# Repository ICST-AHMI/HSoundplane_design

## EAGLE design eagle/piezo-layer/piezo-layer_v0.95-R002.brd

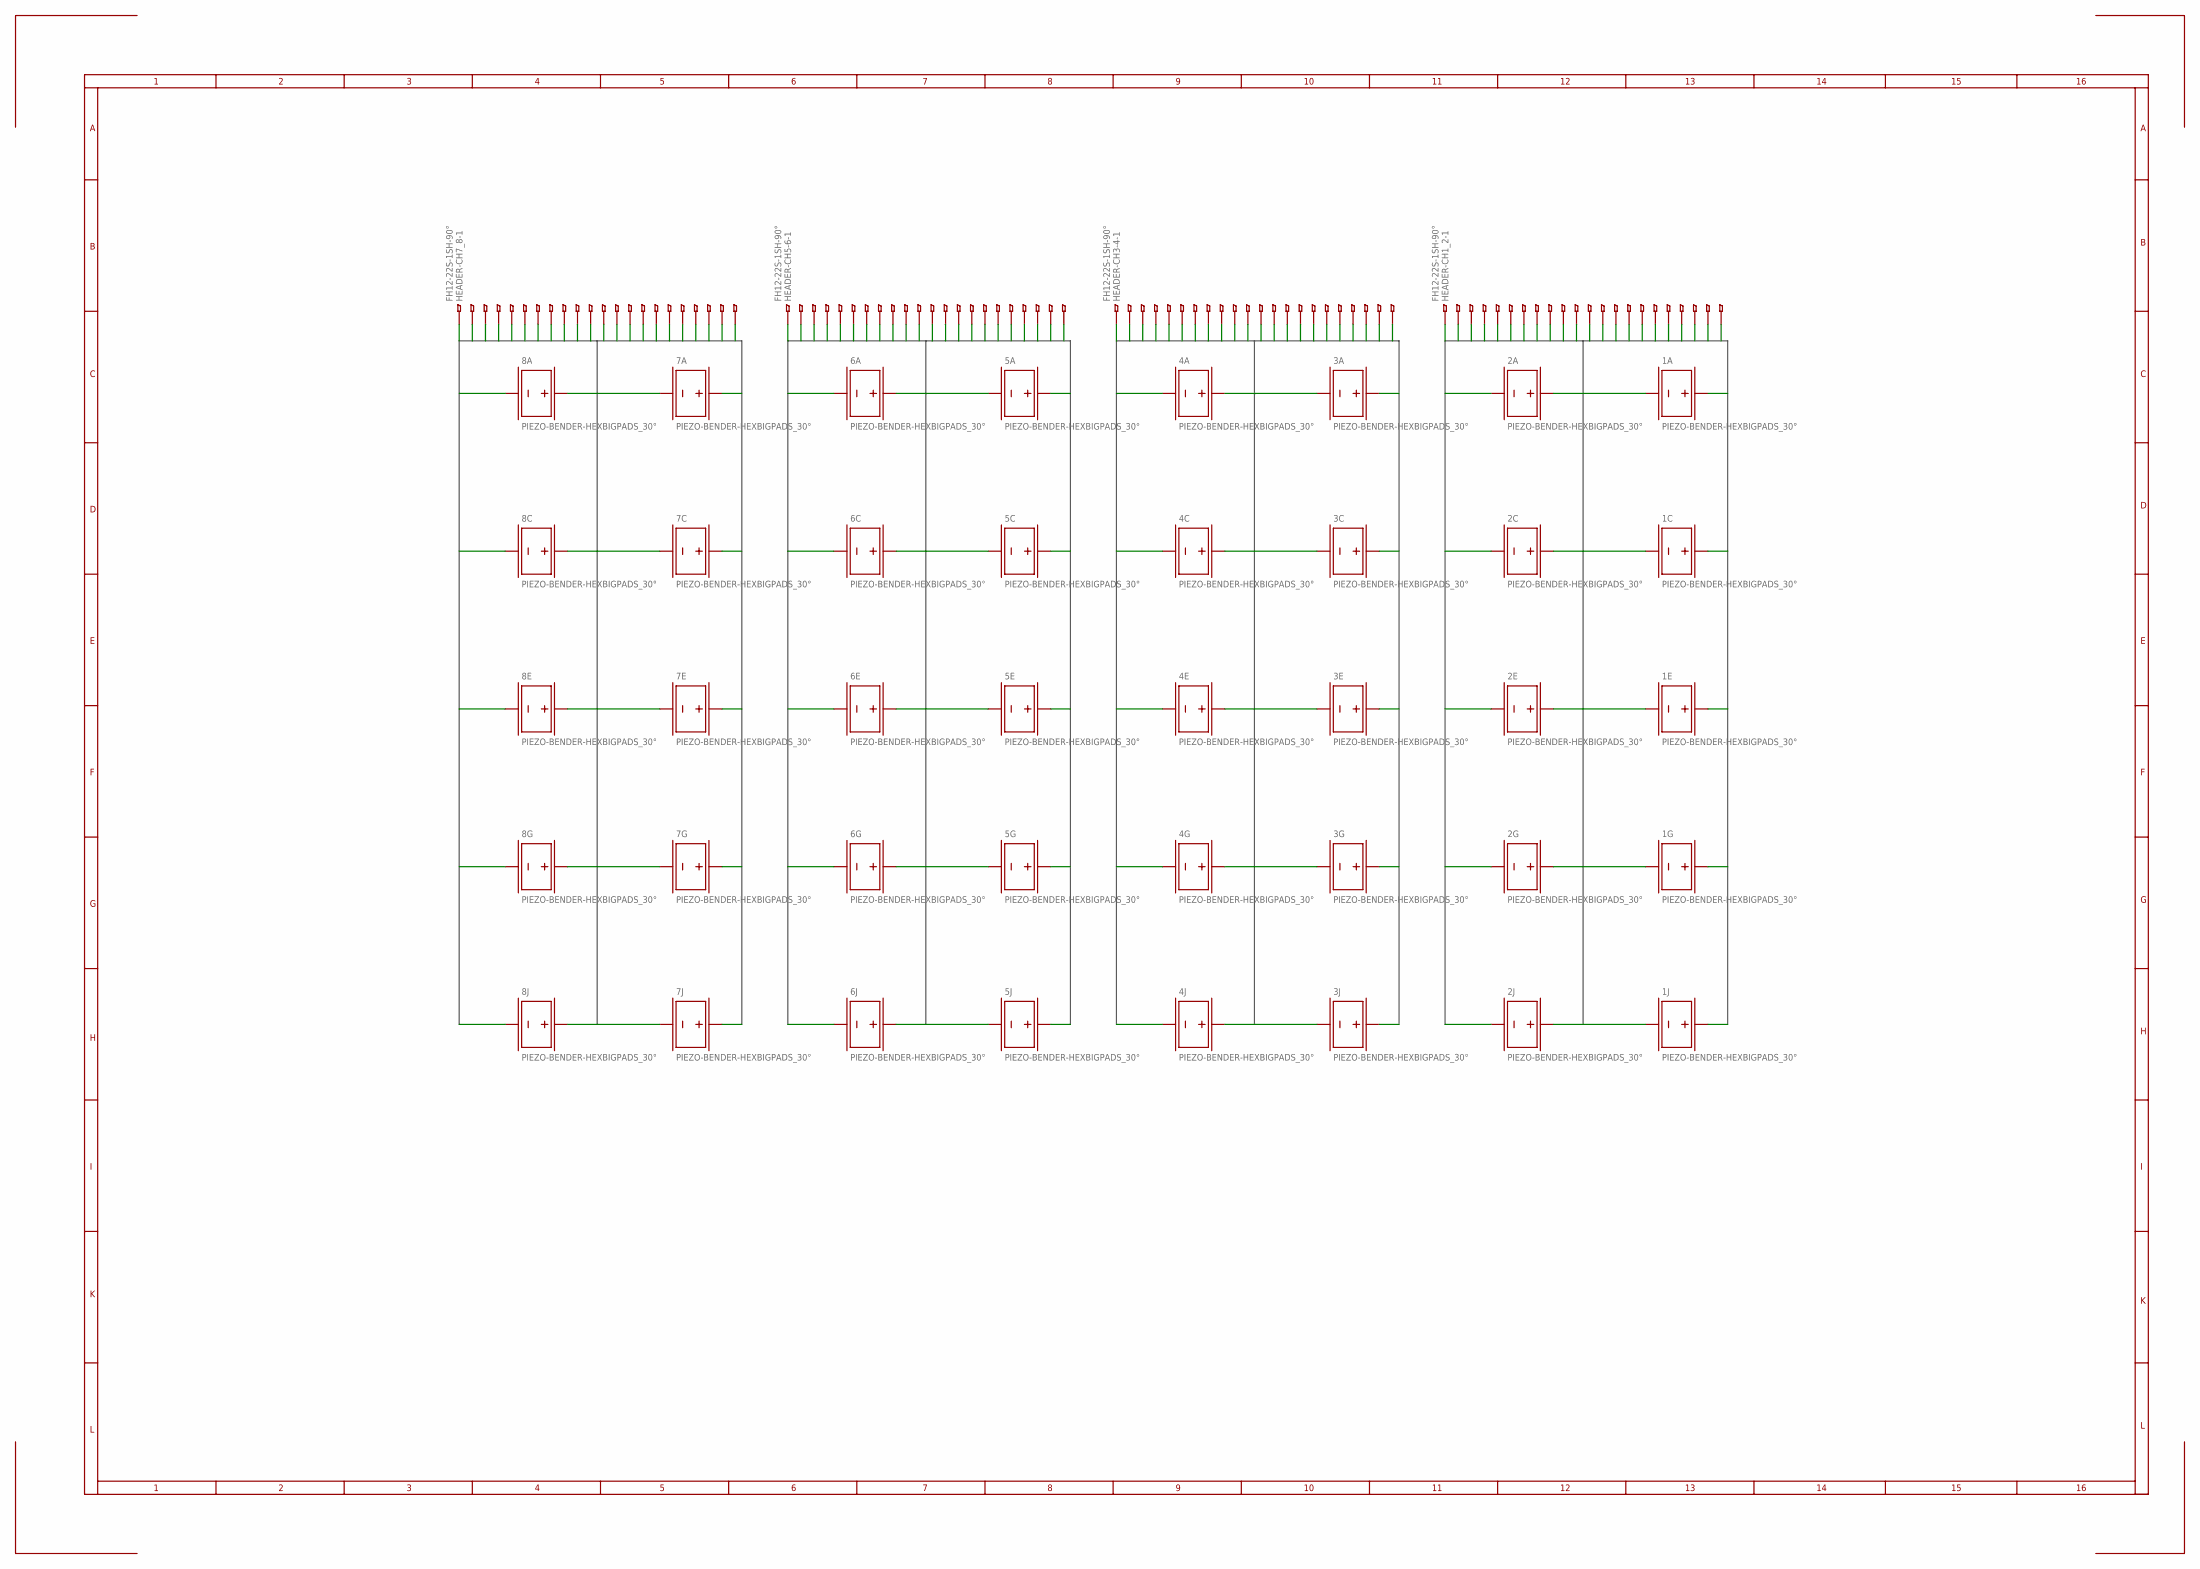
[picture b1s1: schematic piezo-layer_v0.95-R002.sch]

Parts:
1A, 1C, 1E, 1G, 1J, 2A, 2C, 2E, 2G, 2J, 3A, 3C, 3E, 3G, 3J, 4A, 4C, 4E, 4G, 4J, 5A, 5C, 5E, 5G, 5J, 6A, 6C, 6E, 6G, 6J, 7A, 7C, 7E, 7G, 7J, 8A, 8C, 8E, 8G, 8J: PIEZO-BENDER-HEXBIGPADS_30°; PIEZO-BENDER-HEX_16MM_BIGPAD-30°
HEADER-CH1_2, HEADER-CH3-4, HEADER-CH5-6, HEADER-CH7_8: FH12-22S-1SH-90°; FH12-22S-1SH

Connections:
BUS1: 1A.TOP (+_1), HEADER-CH1_2.22
BUS2: HEADER-CH1_2.21
BUS3: 1C.TOP (+_1), HEADER-CH1_2.20
BUS4: HEADER-CH1_2.19
BUS5: 1A.BOTTOM (-_1), 1C.BOTTOM (-_1), 1E.BOTTOM (-_1), 1G.BOTTOM (-_1), 1J.BOTTOM (-_1), HEADER-CH1_2.12, HEADER-CH1_2.18
BUS6: 1E.TOP (+_1), HEADER-CH1_2.17
BUS7: HEADER-CH1_2.16
BUS8: 1G.TOP (+_1), HEADER-CH1_2.15
BUS9: HEADER-CH1_2.14
BUS10: 1J.TOP (+_1), HEADER-CH1_2.13
BUS11: 2A.TOP (+_1), HEADER-CH1_2.11
BUS12: HEADER-CH1_2.10
BUS13: 2C.TOP (+_1), HEADER-CH1_2.9
BUS14: HEADER-CH1_2.8
BUS15: 2A.BOTTOM (-_1), 2C.BOTTOM (-_1), 2E.BOTTOM (-_1), 2G.BOTTOM (-_1), 2J.BOTTOM (-_1), HEADER-CH1_2.1, HEADER-CH1_2.7
BUS16: 2E.TOP (+_1), HEADER-CH1_2.6
BUS17: HEADER-CH1_2.5
BUS18: 2G.TOP (+_1), HEADER-CH1_2.4
BUS19: HEADER-CH1_2.3
BUS20: 2J.TOP (+_1), HEADER-CH1_2.2
BUS21: 3A.TOP (+_1), HEADER-CH3-4.22
BUS22: HEADER-CH3-4.21
BUS23: 3C.TOP (+_1), HEADER-CH3-4.20
BUS24: HEADER-CH3-4.19
BUS25: 3A.BOTTOM (-_1), 3C.BOTTOM (-_1), 3E.BOTTOM (-_1), 3G.BOTTOM (-_1), 3J.BOTTOM (-_1), HEADER-CH3-4.12, HEADER-CH3-4.18
BUS26: 3E.TOP (+_1), HEADER-CH3-4.17
BUS27: HEADER-CH3-4.16
BUS28: 3G.TOP (+_1), HEADER-CH3-4.15
BUS29: HEADER-CH3-4.14
BUS30: 3J.TOP (+_1), HEADER-CH3-4.13
BUS31: 4A.TOP (+_1), HEADER-CH3-4.11
BUS32: HEADER-CH3-4.10
BUS33: 4C.TOP (+_1), HEADER-CH3-4.9
BUS34: HEADER-CH3-4.8
BUS35: 4A.BOTTOM (-_1), 4C.BOTTOM (-_1), 4E.BOTTOM (-_1), 4G.BOTTOM (-_1), 4J.BOTTOM (-_1), HEADER-CH3-4.1, HEADER-CH3-4.7
BUS36: 4E.TOP (+_1), HEADER-CH3-4.6
BUS37: HEADER-CH3-4.5
BUS38: 4G.TOP (+_1), HEADER-CH3-4.4
BUS39: HEADER-CH3-4.3
BUS40: 4J.TOP (+_1), HEADER-CH3-4.2
BUS41: 5A.TOP (+_1), HEADER-CH5-6.22
BUS42: HEADER-CH5-6.21
BUS43: 5C.TOP (+_1), HEADER-CH5-6.20
BUS44: HEADER-CH5-6.19
BUS45: 5A.BOTTOM (-_1), 5C.BOTTOM (-_1), 5E.BOTTOM (-_1), 5G.BOTTOM (-_1), 5J.BOTTOM (-_1), HEADER-CH5-6.12, HEADER-CH5-6.18
BUS46: 5E.TOP (+_1), HEADER-CH5-6.17
BUS47: HEADER-CH5-6.16
BUS48: 5G.TOP (+_1), HEADER-CH5-6.15
BUS49: HEADER-CH5-6.14
BUS50: 5J.TOP (+_1), HEADER-CH5-6.13
BUS51: 6A.TOP (+_1), HEADER-CH5-6.11
BUS52: HEADER-CH5-6.10
BUS53: 6C.TOP (+_1), HEADER-CH5-6.9
BUS54: HEADER-CH5-6.8
BUS55: 6A.BOTTOM (-_1), 6C.BOTTOM (-_1), 6E.BOTTOM (-_1), 6G.BOTTOM (-_1), 6J.BOTTOM (-_1), HEADER-CH5-6.1, HEADER-CH5-6.7
BUS56: 6E.TOP (+_1), HEADER-CH5-6.6
BUS57: HEADER-CH5-6.5
BUS58: 6G.TOP (+_1), HEADER-CH5-6.4
BUS59: HEADER-CH5-6.3
BUS60: 6J.TOP (+_1), HEADER-CH5-6.2
BUS61: 7A.TOP (+_1), HEADER-CH7_8.22
BUS62: HEADER-CH7_8.21
BUS63: 7C.TOP (+_1), HEADER-CH7_8.20
BUS64: HEADER-CH7_8.19
BUS65: 7A.BOTTOM (-_1), 7C.BOTTOM (-_1), 7E.BOTTOM (-_1), 7G.BOTTOM (-_1), 7J.BOTTOM (-_1), HEADER-CH7_8.12, HEADER-CH7_8.18
BUS66: 7E.TOP (+_1), HEADER-CH7_8.17
BUS67: HEADER-CH7_8.16
BUS68: 7G.TOP (+_1), HEADER-CH7_8.15
BUS69: HEADER-CH7_8.14
BUS70: 7J.TOP (+_1), HEADER-CH7_8.13
BUS71: 8A.TOP (+_1), HEADER-CH7_8.11
BUS72: HEADER-CH7_8.10
BUS73: 8C.TOP (+_1), HEADER-CH7_8.9
BUS74: HEADER-CH7_8.8
BUS75: 8A.BOTTOM (-_1), 8C.BOTTOM (-_1), 8E.BOTTOM (-_1), 8G.BOTTOM (-_1), 8J.BOTTOM (-_1), HEADER-CH7_8.1, HEADER-CH7_8.7
BUS76: 8E.TOP (+_1), HEADER-CH7_8.6
BUS77: HEADER-CH7_8.5
BUS78: 8G.TOP (+_1), HEADER-CH7_8.4
BUS79: HEADER-CH7_8.3
BUS80: 8J.TOP (+_1), HEADER-CH7_8.2

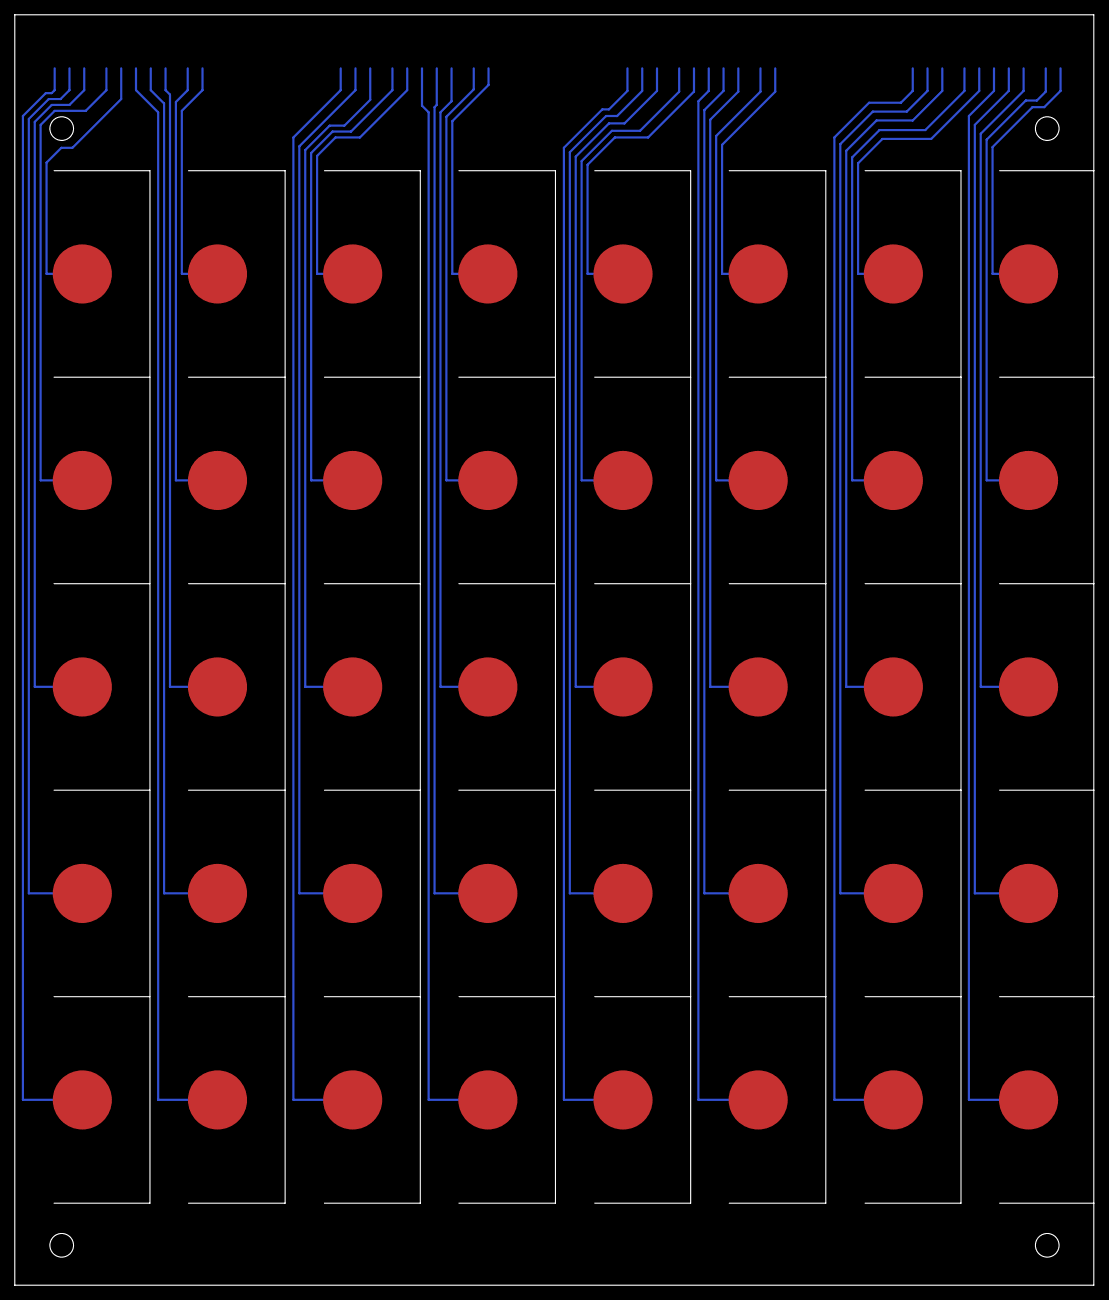
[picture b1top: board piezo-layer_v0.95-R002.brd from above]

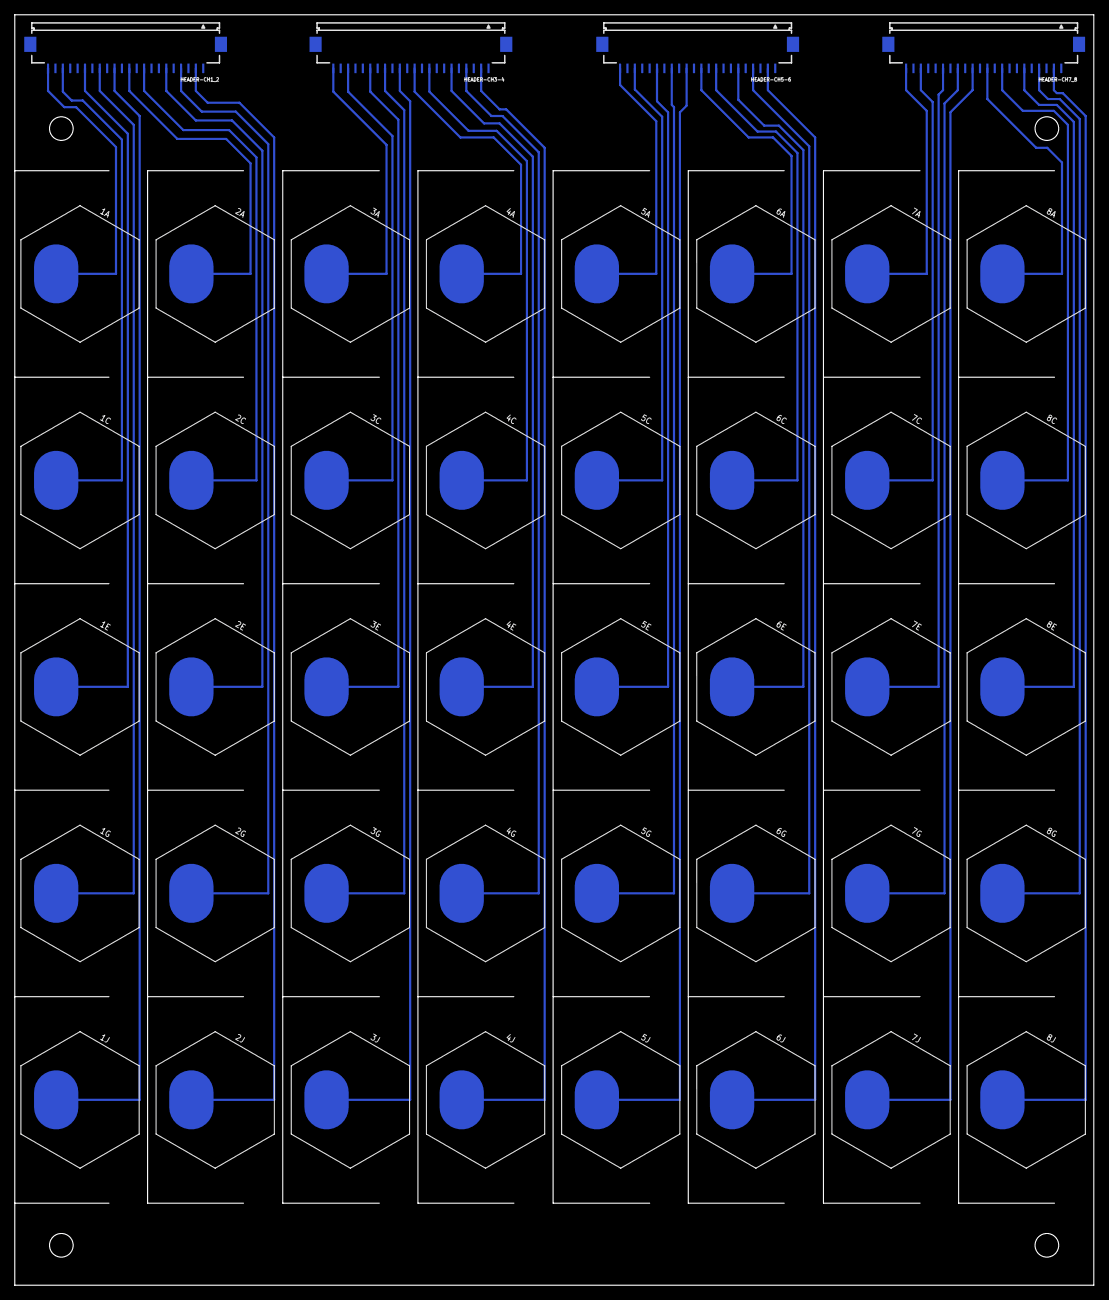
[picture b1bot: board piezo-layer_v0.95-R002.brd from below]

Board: 2 copper layers, 146.0 x 171.9 mm, 44 parts (44 on the bottom side), 48 nets.

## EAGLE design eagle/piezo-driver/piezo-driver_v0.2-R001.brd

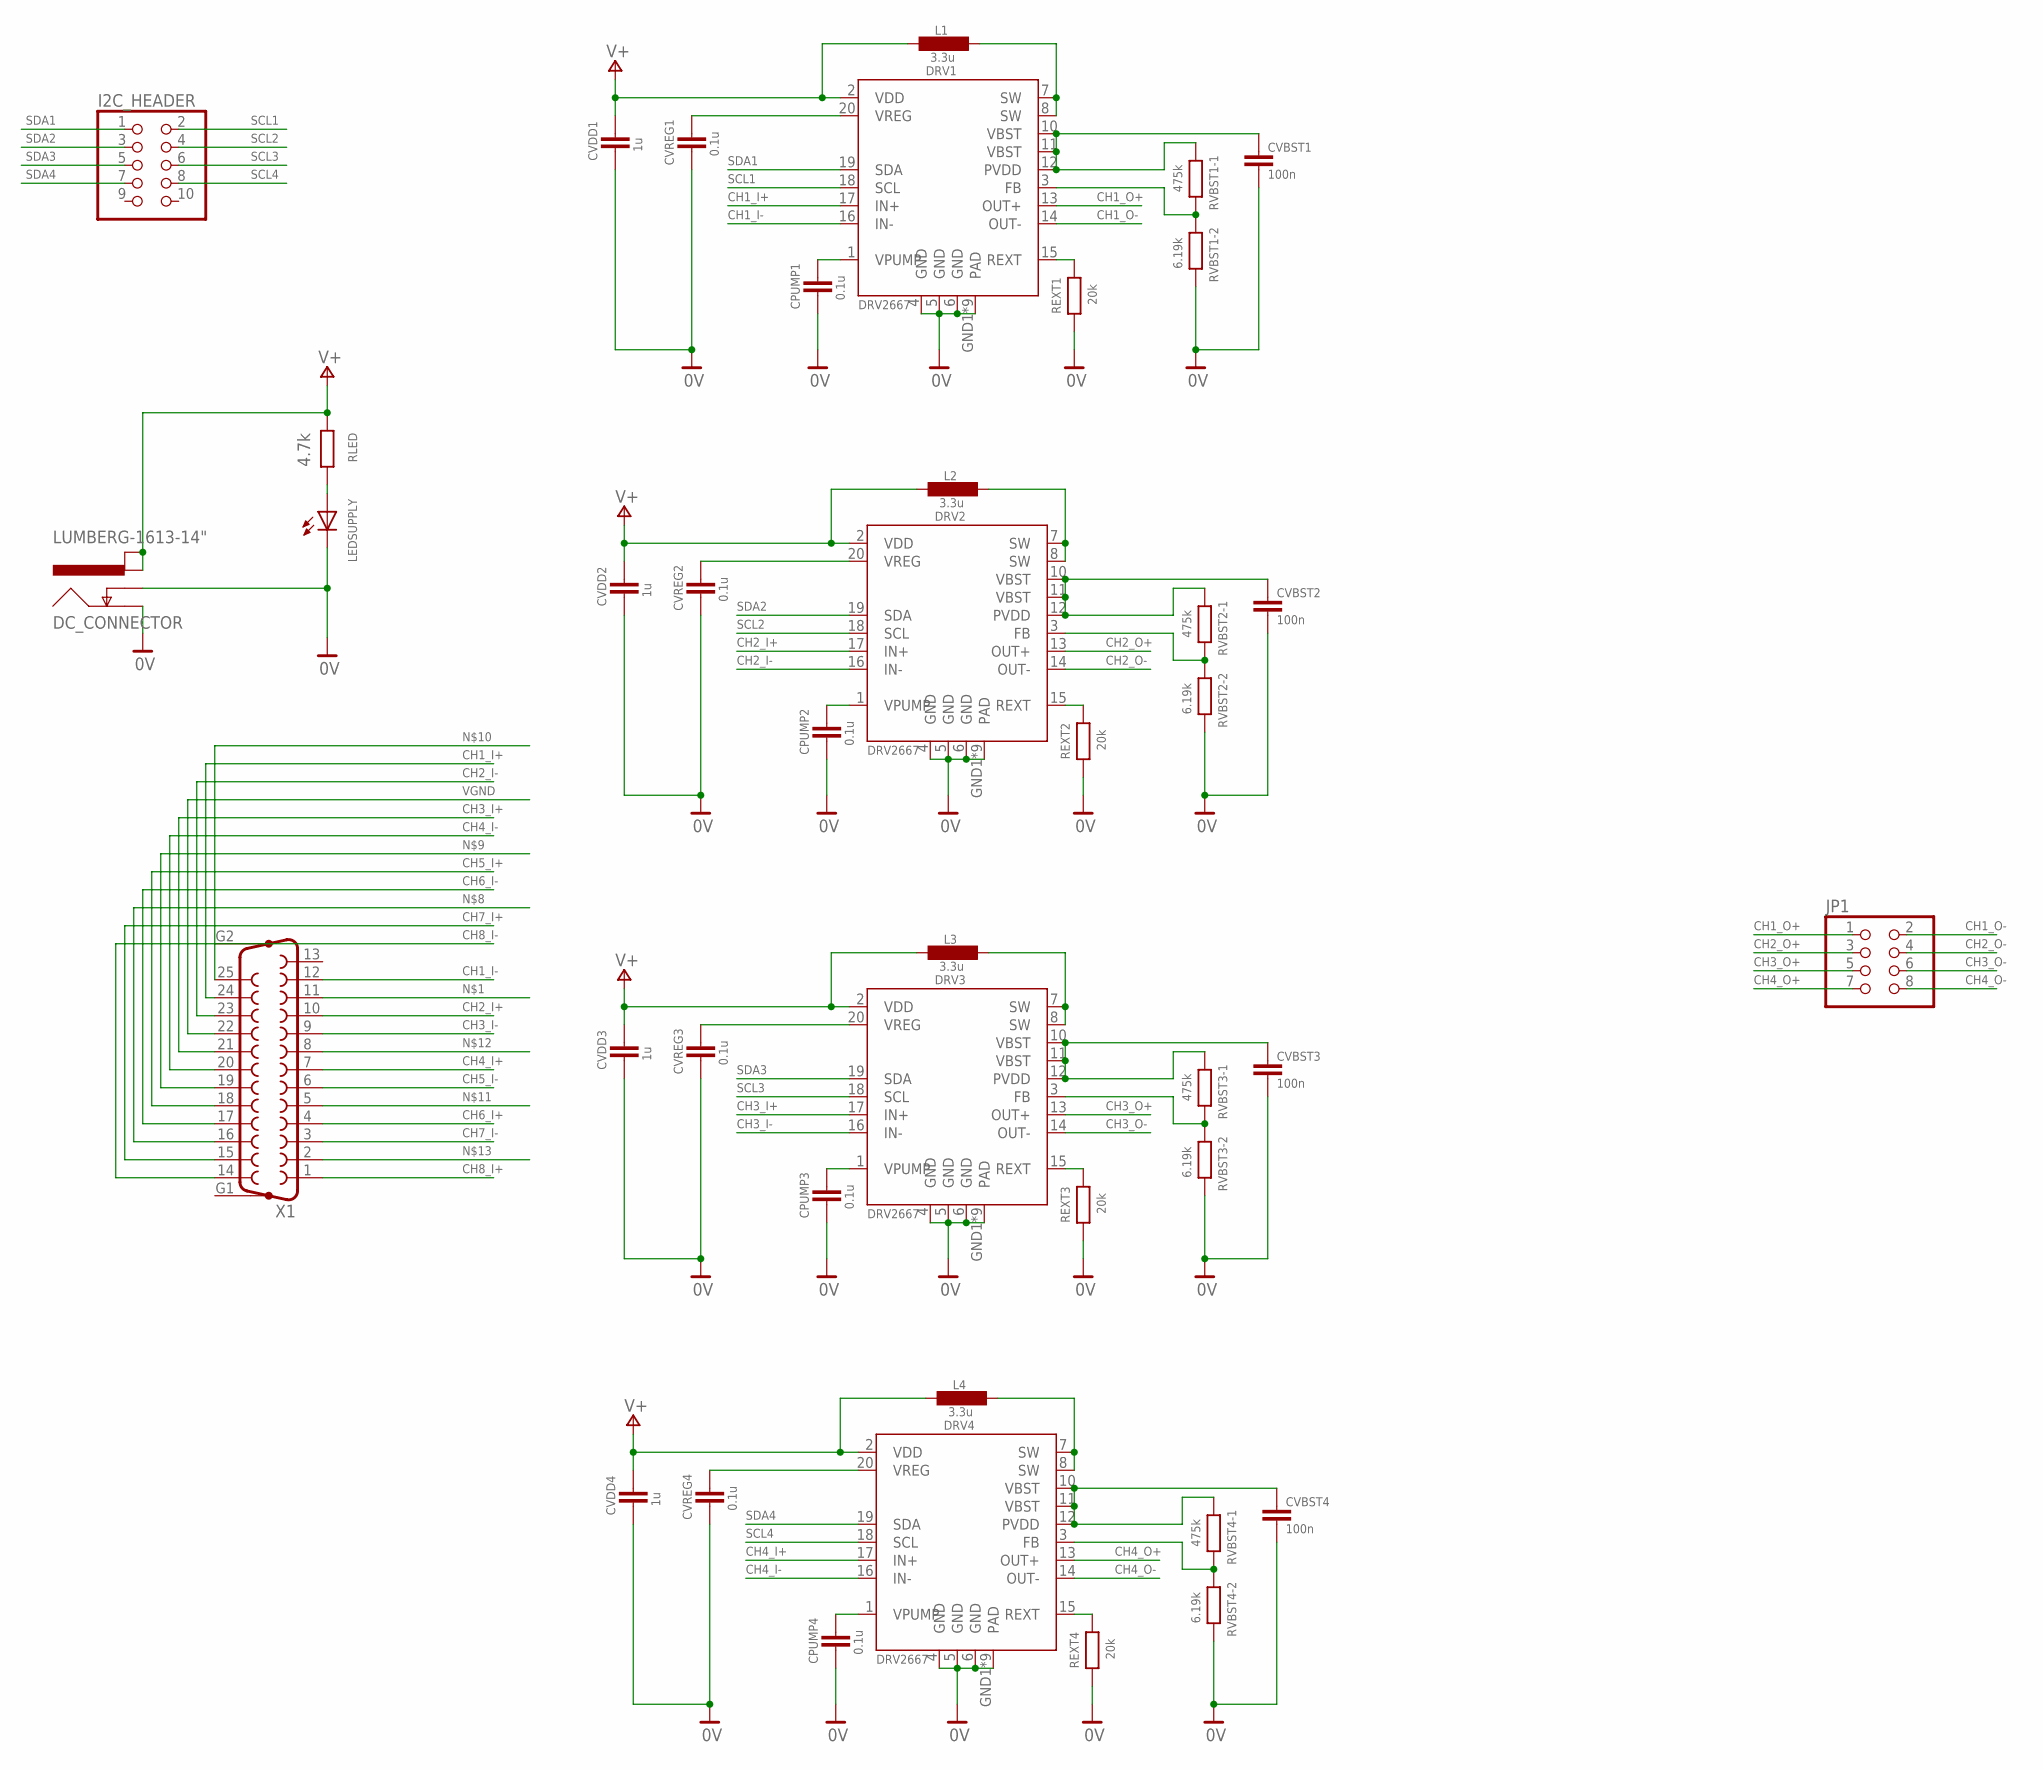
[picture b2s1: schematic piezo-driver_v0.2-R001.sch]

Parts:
CPUMP1, CPUMP2, CPUMP3, CPUMP4: 0.1u; C0805
CVBST1, CVBST2, CVBST3, CVBST4: 100n; C0805
CVDD1, CVDD2, CVDD3, CVDD4: 1u; C0805
CVREG1, CVREG2, CVREG3, CVREG4: 0.1u; C0805
DC_CONNECTOR: LUMBERG-1613-14"; LUMBERG-1613_14
DRV1, DRV2, DRV3, DRV4: DRV2667QFN; QFN400X400
I2C_HEADER: HEADER_2X52.54_FEMALE; 2X05_2.54
JP1: PINHD-2X4/90; 2X04/90
L1, L2, L3, L4: 3.3u; L3225M
LEDSUPPLY: LED0603; LED-0603
REXT1, REXT2, REXT3, REXT4: 20k; R0805
RLED: 4.7k; R0805
RVBST1-1, RVBST2-1, RVBST3-1, RVBST4-1: 475k; R0805
RVBST1-2, RVBST2-2, RVBST3-2, RVBST4-2: 6.19k; R0805
X1: F25HP

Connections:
0V: CPUMP1.2, CPUMP2.2, CPUMP3.2, CPUMP4.2, CVBST1.2, CVBST2.2, CVBST3.2, CVBST4.2, CVDD1.2, CVDD2.2, CVDD3.2, CVDD4.2, CVREG1.2, CVREG2.2, CVREG3.2, CVREG4.2, DC_CONNECTOR.1 (GND), DC_CONNECTOR.2 (GND_INS), DRV1.4 (GND), DRV1.5 (GND), DRV1.6 (GND), DRV1.GND1 (PAD), DRV1.GND2 (PAD), DRV1.GND3 (PAD), DRV1.GND4 (PAD), DRV1.GND5 (PAD), DRV1.GND6 (PAD), DRV1.GND7 (PAD), DRV1.GND8 (PAD), DRV1.GND9 (PAD), DRV2.4 (GND), DRV2.5 (GND), DRV2.6 (GND), DRV2.GND1 (PAD), DRV2.GND2 (PAD), DRV2.GND3 (PAD), DRV2.GND4 (PAD), DRV2.GND5 (PAD), DRV2.GND6 (PAD), DRV2.GND7 (PAD), DRV2.GND8 (PAD), DRV2.GND9 (PAD), DRV3.4 (GND), DRV3.5 (GND), DRV3.6 (GND), DRV3.GND1 (PAD), DRV3.GND2 (PAD), DRV3.GND3 (PAD), DRV3.GND4 (PAD), DRV3.GND5 (PAD), DRV3.GND6 (PAD), DRV3.GND7 (PAD), DRV3.GND8 (PAD), DRV3.GND9 (PAD), DRV4.4 (GND), DRV4.5 (GND), DRV4.6 (GND), DRV4.GND1 (PAD), DRV4.GND2 (PAD), DRV4.GND3 (PAD), DRV4.GND4 (PAD), DRV4.GND5 (PAD), DRV4.GND6 (PAD), DRV4.GND7 (PAD), DRV4.GND8 (PAD), DRV4.GND9 (PAD), LEDSUPPLY.C, REXT1.1, REXT2.1, REXT3.1, REXT4.1, RVBST1-2.1, RVBST2-2.1, RVBST3-2.1, RVBST4-2.1
CH1_I+: DRV1.17 (IN+), X1.24
CH1_I-: DRV1.16 (IN-), X1.12
CH1_O+: DRV1.13 (OUT+), JP1.1
CH1_O-: DRV1.14 (OUT-), JP1.2
CH2_I+: DRV2.17 (IN+), X1.10
CH2_I-: DRV2.16 (IN-), X1.23
CH2_O+: DRV2.13 (OUT+), JP1.3
CH2_O-: DRV2.14 (OUT-), JP1.4
CH3_I+: DRV3.17 (IN+), X1.21
CH3_I-: DRV3.16 (IN-), X1.9
CH3_O+: DRV3.13 (OUT+), JP1.5
CH3_O-: DRV3.14 (OUT-), JP1.6
CH4_I+: DRV4.17 (IN+), X1.7
CH4_I-: DRV4.16 (IN-), X1.20
CH4_O+: DRV4.13 (OUT+), JP1.7
CH4_O-: DRV4.14 (OUT-), JP1.8
CH5_I+: X1.18
CH5_I-: X1.6
CH6_I+: X1.4
CH6_I-: X1.17
CH7_I+: X1.15
CH7_I-: X1.3
CH8_I+: X1.1
CH8_I-: X1.14
unnamed: DRV1.7 (SW), DRV1.8 (SW), L1.1
unnamed: CVBST1.1, DRV1.10 (VBST), DRV1.11 (VBST), DRV1.12 (PVDD), RVBST1-1.2
unnamed: DRV1.3 (FB), RVBST1-1.1, RVBST1-2.2
unnamed: DRV1.15 (REXT), REXT1.2
unnamed: CPUMP1.1, DRV1.1 (VPUMP)
unnamed: CVREG1.1, DRV1.20 (VREG)
unnamed: LEDSUPPLY.A, RLED.1
unnamed: DRV2.7 (SW), DRV2.8 (SW), L2.1
unnamed: CVBST2.1, DRV2.10 (VBST), DRV2.11 (VBST), DRV2.12 (PVDD), RVBST2-1.2
unnamed: DRV2.3 (FB), RVBST2-1.1, RVBST2-2.2
unnamed: DRV2.15 (REXT), REXT2.2
unnamed: CPUMP2.1, DRV2.1 (VPUMP)
unnamed: CVREG2.1, DRV2.20 (VREG)
unnamed: DRV3.7 (SW), DRV3.8 (SW), L3.1
unnamed: CVBST3.1, DRV3.10 (VBST), DRV3.11 (VBST), DRV3.12 (PVDD), RVBST3-1.2
unnamed: DRV3.3 (FB), RVBST3-1.1, RVBST3-2.2
unnamed: DRV3.15 (REXT), REXT3.2
unnamed: CPUMP3.1, DRV3.1 (VPUMP)
unnamed: CVREG3.1, DRV3.20 (VREG)
unnamed: DRV4.7 (SW), DRV4.8 (SW), L4.1
unnamed: CVBST4.1, DRV4.10 (VBST), DRV4.11 (VBST), DRV4.12 (PVDD), RVBST4-1.2
unnamed: DRV4.3 (FB), RVBST4-1.1, RVBST4-2.2
unnamed: DRV4.15 (REXT), REXT4.2
unnamed: CPUMP4.1, DRV4.1 (VPUMP)
unnamed: CVREG4.1, DRV4.20 (VREG)
SCL1: DRV1.18 (SCL), I2C_HEADER.2
SCL2: DRV2.18 (SCL), I2C_HEADER.4
SCL3: DRV3.18 (SCL), I2C_HEADER.6
SCL4: DRV4.18 (SCL), I2C_HEADER.8
SDA1: DRV1.19 (SDA), I2C_HEADER.1
SDA2: DRV2.19 (SDA), I2C_HEADER.3
SDA3: DRV3.19 (SDA), I2C_HEADER.5
SDA4: DRV4.19 (SDA), I2C_HEADER.7
V+: CVDD1.1, CVDD2.1, CVDD3.1, CVDD4.1, DC_CONNECTOR.3 (PWR_1), DC_CONNECTOR.4 (PWR_2), DRV1.2 (VDD), DRV2.2 (VDD), DRV3.2 (VDD), DRV4.2 (VDD), L1.2, L2.2, L3.2, L4.2, RLED.2
VGND: X1.22

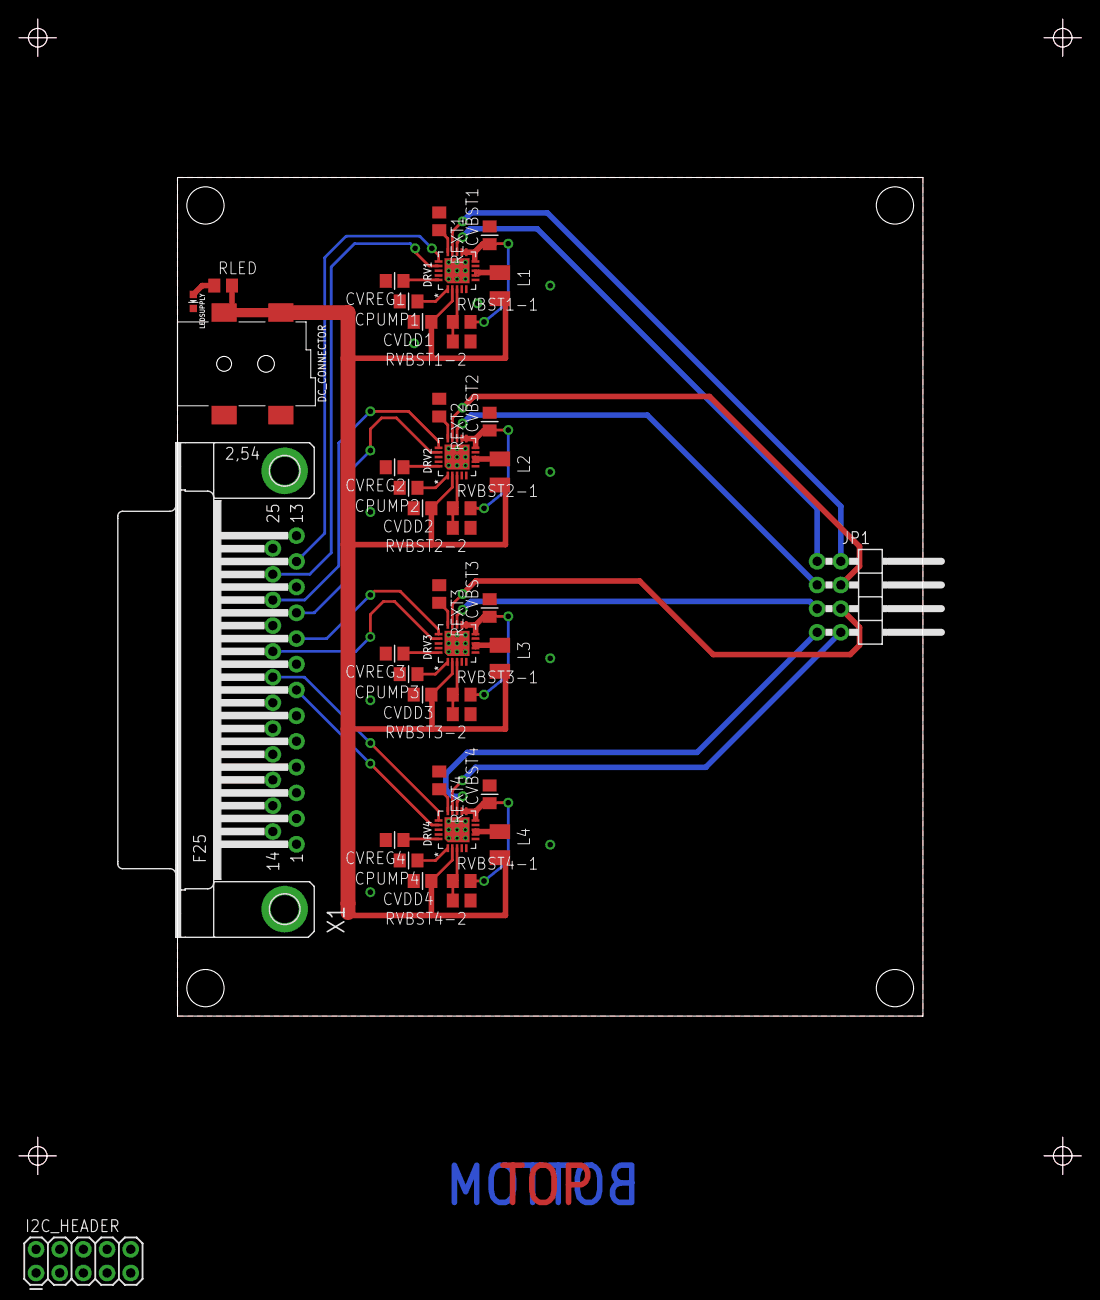
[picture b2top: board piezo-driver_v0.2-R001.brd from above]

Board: 2 copper layers, 80.0 x 90.0 mm, 42 parts (0 on the bottom side), 51 nets.

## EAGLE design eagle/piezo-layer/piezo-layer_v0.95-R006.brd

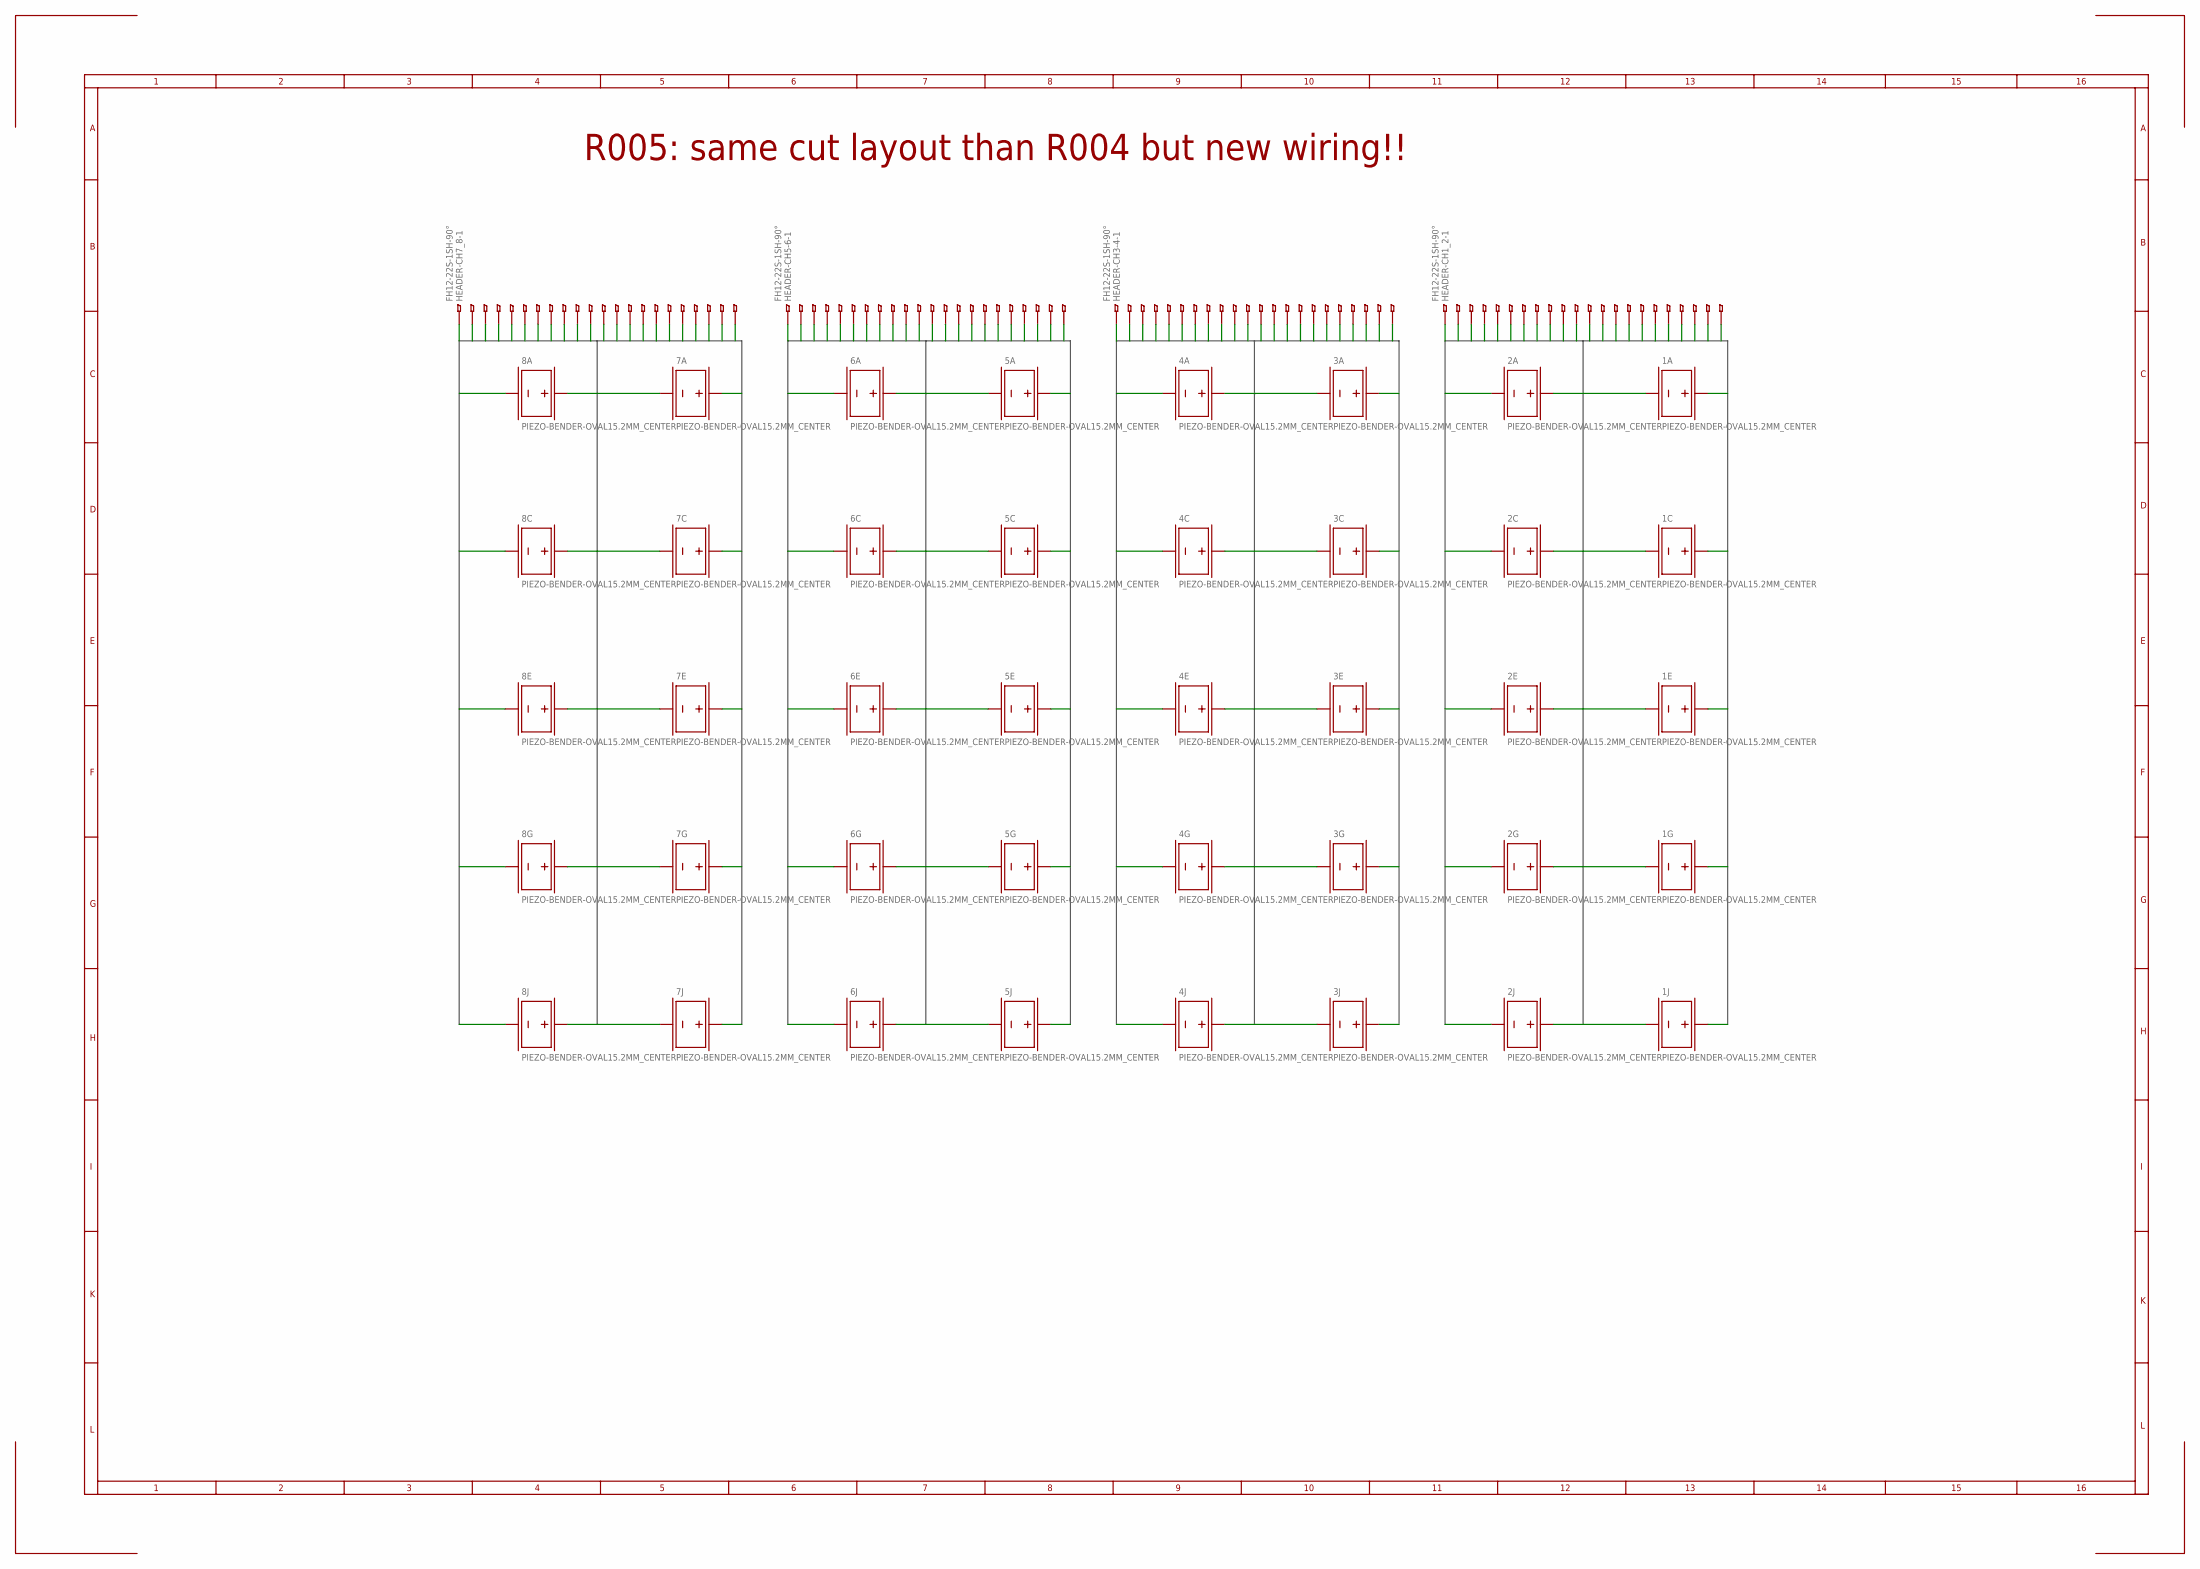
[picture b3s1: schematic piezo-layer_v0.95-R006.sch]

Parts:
1A, 1C, 1E, 1G, 1J, 2A, 2C, 2E, 2G, 2J, 3A, 3C, 3E, 3G, 3J, 4A, 4C, 4E, 4G, 4J, 5A, 5C, 5E, 5G, 5J, 6A, 6C, 6E, 6G, 6J, 7A, 7C, 7E, 7G, 7J, 8A, 8C, 8E, 8G, 8J: PIEZO-BENDER-OVAL15.2MM_CENTER; PIEZO-BENDER-OVAL_15.2MM_BIGPADS_CENTER
HEADER-CH1_2, HEADER-CH3-4, HEADER-CH5-6, HEADER-CH7_8: FH12-22S-1SH-90°; FH12-22S-1SH

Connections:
BUS1: 1J.TOP (+_1), HEADER-CH1_2.21
BUS2: HEADER-CH1_2.20
BUS3: 1G.TOP (+_1), HEADER-CH1_2.19
BUS4: HEADER-CH1_2.18
BUS5: 1A.BOTTOM (-_1), 1C.BOTTOM (-_1), 1E.BOTTOM (-_1), 1G.BOTTOM (-_1), 1J.BOTTOM (-_1), HEADER-CH1_2.16, HEADER-CH1_2.22
BUS6: 1E.TOP (+_1), HEADER-CH1_2.17
BUS7: HEADER-CH1_2.15
BUS8: 1C.TOP (+_1), HEADER-CH1_2.14
BUS9: HEADER-CH1_2.13
BUS10: 1A.TOP (+_1), HEADER-CH1_2.12
BUS11: 2J.TOP (+_1), HEADER-CH1_2.10
BUS12: HEADER-CH1_2.9
BUS13: 2G.TOP (+_1), HEADER-CH1_2.8
BUS14: HEADER-CH1_2.7
BUS15: 2A.BOTTOM (-_1), 2C.BOTTOM (-_1), 2E.BOTTOM (-_1), 2G.BOTTOM (-_1), 2J.BOTTOM (-_1), HEADER-CH1_2.5, HEADER-CH1_2.11
BUS16: 2E.TOP (+_1), HEADER-CH1_2.6
BUS17: HEADER-CH1_2.4
BUS18: 2C.TOP (+_1), HEADER-CH1_2.3
BUS19: HEADER-CH1_2.2
BUS20: 2A.TOP (+_1), HEADER-CH1_2.1
BUS21: 3J.TOP (+_1), HEADER-CH3-4.21
BUS22: HEADER-CH3-4.20
BUS23: 3G.TOP (+_1), HEADER-CH3-4.19
BUS24: HEADER-CH3-4.18
BUS25: 3A.BOTTOM (-_1), 3C.BOTTOM (-_1), 3E.BOTTOM (-_1), 3G.BOTTOM (-_1), 3J.BOTTOM (-_1), HEADER-CH3-4.16, HEADER-CH3-4.22
BUS26: 3E.TOP (+_1), HEADER-CH3-4.17
BUS27: HEADER-CH3-4.15
BUS28: 3C.TOP (+_1), HEADER-CH3-4.14
BUS29: HEADER-CH3-4.13
BUS30: 3A.TOP (+_1), HEADER-CH3-4.12
BUS31: 4J.TOP (+_1), HEADER-CH3-4.10
BUS32: HEADER-CH3-4.9
BUS33: 4G.TOP (+_1), HEADER-CH3-4.8
BUS34: HEADER-CH3-4.7
BUS35: 4A.BOTTOM (-_1), 4C.BOTTOM (-_1), 4E.BOTTOM (-_1), 4G.BOTTOM (-_1), 4J.BOTTOM (-_1), HEADER-CH3-4.5, HEADER-CH3-4.11
BUS36: 4E.TOP (+_1), HEADER-CH3-4.6
BUS37: HEADER-CH3-4.4
BUS38: 4C.TOP (+_1), HEADER-CH3-4.3
BUS39: HEADER-CH3-4.2
BUS40: 4A.TOP (+_1), HEADER-CH3-4.1
BUS41: 5J.TOP (+_1), HEADER-CH5-6.21
BUS42: HEADER-CH5-6.20
BUS43: 5G.TOP (+_1), HEADER-CH5-6.19
BUS44: HEADER-CH5-6.18
BUS45: 5A.BOTTOM (-_1), 5C.BOTTOM (-_1), 5E.BOTTOM (-_1), 5G.BOTTOM (-_1), 5J.BOTTOM (-_1), HEADER-CH5-6.16, HEADER-CH5-6.22
BUS46: 5E.TOP (+_1), HEADER-CH5-6.17
BUS47: HEADER-CH5-6.15
BUS48: 5C.TOP (+_1), HEADER-CH5-6.14
BUS49: HEADER-CH5-6.13
BUS50: 5A.TOP (+_1), HEADER-CH5-6.12
BUS51: 6J.TOP (+_1), HEADER-CH5-6.10
BUS52: HEADER-CH5-6.9
BUS53: 6G.TOP (+_1), HEADER-CH5-6.8
BUS54: HEADER-CH5-6.7
BUS55: 6A.BOTTOM (-_1), 6C.BOTTOM (-_1), 6E.BOTTOM (-_1), 6G.BOTTOM (-_1), 6J.BOTTOM (-_1), HEADER-CH5-6.5, HEADER-CH5-6.11
BUS56: 6E.TOP (+_1), HEADER-CH5-6.6
BUS57: HEADER-CH5-6.4
BUS58: 6C.TOP (+_1), HEADER-CH5-6.3
BUS59: HEADER-CH5-6.2
BUS60: 6A.TOP (+_1), HEADER-CH5-6.1
BUS61: 7J.TOP (+_1), HEADER-CH7_8.21
BUS62: HEADER-CH7_8.20
BUS63: 7G.TOP (+_1), HEADER-CH7_8.19
BUS64: HEADER-CH7_8.18
BUS65: 7A.BOTTOM (-_1), 7C.BOTTOM (-_1), 7E.BOTTOM (-_1), 7G.BOTTOM (-_1), 7J.BOTTOM (-_1), HEADER-CH7_8.16, HEADER-CH7_8.22
BUS66: 7E.TOP (+_1), HEADER-CH7_8.17
BUS67: HEADER-CH7_8.15
BUS68: 7C.TOP (+_1), HEADER-CH7_8.14
BUS69: HEADER-CH7_8.13
BUS70: 7A.TOP (+_1), HEADER-CH7_8.12
BUS71: 8J.TOP (+_1), HEADER-CH7_8.10
BUS72: HEADER-CH7_8.9
BUS73: 8G.TOP (+_1), HEADER-CH7_8.8
BUS74: HEADER-CH7_8.7
BUS75: 8A.BOTTOM (-_1), 8C.BOTTOM (-_1), 8E.BOTTOM (-_1), 8G.BOTTOM (-_1), 8J.BOTTOM (-_1), HEADER-CH7_8.5, HEADER-CH7_8.11
BUS76: 8E.TOP (+_1), HEADER-CH7_8.6
BUS77: HEADER-CH7_8.4
BUS78: 8C.TOP (+_1), HEADER-CH7_8.3
BUS79: HEADER-CH7_8.2
BUS80: 8A.TOP (+_1), HEADER-CH7_8.1

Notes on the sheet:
R005: same cut layout than R004 but new wiring!!

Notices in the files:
eagle/piezo-driver/piezo-driver_v0.95-R003.brd:
(c) 2015 ICST
